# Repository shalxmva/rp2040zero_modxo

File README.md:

# rp2040zero_modxo
rp2040zero carrier board for modxo

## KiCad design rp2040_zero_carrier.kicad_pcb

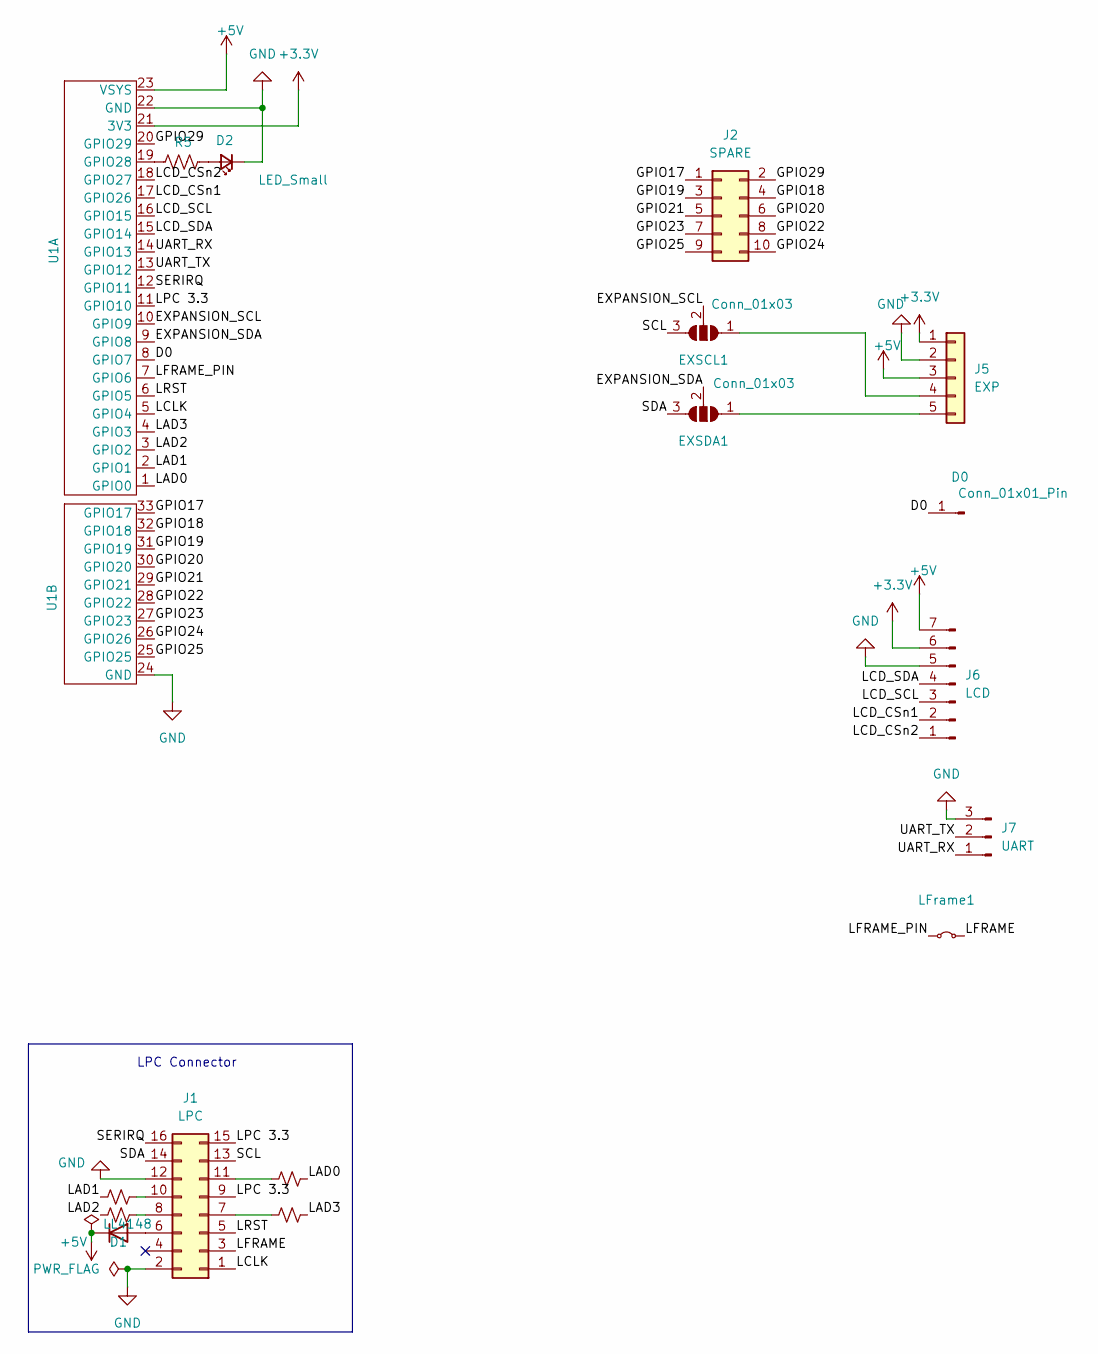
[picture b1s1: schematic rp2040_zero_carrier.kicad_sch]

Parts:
D0: Conn_01x01_Pin; SolderJumper-2_P1.3mm_Bridged2Bar_RoundedPad1.0x1.5mm
D1: LL4148; D_MiniMELF
D2: LED_Small; LED_0805_2012Metric_Pad1.15x1.40mm_HandSolder
EXSCL1: Conn_01x03; SolderJumper-3_P1.3mm_Bridged12_RoundedPad1.0x1.5mm
EXSDA1: Conn_01x03; SolderJumper-3_P1.3mm_Bridged12_RoundedPad1.0x1.5mm
J1: LPC; PinSocket_2x08_P2.54mm_Vertical
J2: SPARE; PinHeader_2x05_P2.54mm_Vertical
J5: EXP; PinHeader_1x05_P2.54mm_Vertical
J6: LCD; PinHeader_1x07_P2.54mm_Vertical
J7: UART; PinHeader_1x03_P2.54mm_Vertical
LFrame1: Jumper_2_Small_Bridged; SolderJumper-2_P1.3mm_Bridged_RoundedPad1.0x1.5mm
R1, R2, R3, R4: 100; R_0805_2012Metric_Pad1.20x1.40mm_HandSolder
R5: R_US; R_0805_2012Metric_Pad1.20x1.40mm_HandSolder
U1: RP2040 Zero

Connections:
+3.3V: J5.1, J6.6, U1.21 (3V3)
+5V: D1.1 (K), J5.3, J6.7, U1.23 (VSYS)
/D0: D0.1, U1.8 (GPIO7)
/EXPANSION_SCL: EXSCL1.2 (C), U1.10 (GPIO9)
/EXPANSION_SDA: EXSDA1.2 (C), U1.9 (GPIO8)
/GPIO17: J2.1, U1.33 (GPIO17)
/GPIO18: J2.4, U1.32 (GPIO18)
/GPIO19: J2.3, U1.31 (GPIO19)
/GPIO20: J2.6, U1.30 (GPIO20)
/GPIO21: J2.5, U1.29 (GPIO21)
/GPIO22: J2.8, U1.28 (GPIO22)
/GPIO23: J2.7, U1.27 (GPIO23)
/GPIO24: J2.10, U1.26 (GPIO26)
/GPIO25: J2.9, U1.25 (GPIO25)
/GPIO29: J2.2, U1.20 (GPIO29)
/LAD0: R1.2, U1.1 (GPIO0)
/LAD1: R2.1, U1.2 (GPIO1)
/LAD2: R3.1, U1.3 (GPIO2)
/LAD3: R4.2, U1.4 (GPIO3)
/LCD_CSn1: J6.2, U1.17 (GPIO26)
/LCD_CSn2: J6.1, U1.18 (GPIO27)
/LCD_SCL: J6.3, U1.16 (GPIO15)
/LCD_SDA: J6.4, U1.15 (GPIO14)
/LCLK: J1.1, U1.5 (GPIO4)
/LFRAME: J1.3, LFrame1.2 (B)
/LFRAME_PIN: LFrame1.1 (A), U1.7 (GPIO6)
/LPC 3.3: J1.9, J1.15, U1.11 (GPIO10)
/LRST: J1.5, U1.6 (GPIO5)
/SCL: EXSCL1.3 (B), J1.13
/SDA: EXSDA1.3 (B), J1.14
/SERIRQ: J1.16, U1.12 (GPIO11)
/UART_RX: J7.1, U1.14 (GPIO13)
/UART_TX: J7.2, U1.13 (GPIO12)
GND: D2.1 (K), J1.2, J1.12, J5.2, J6.5, J7.3, U1.22 (GND), U1.24 (GND)
unnamed: D1.2 (A), J1.6
unnamed: D2.2 (A), R5.2
unnamed: EXSCL1.1 (A), J5.4
unnamed: EXSDA1.1 (A), J5.5
unnamed: J1.7, R4.1
unnamed: J1.8, R3.2
unnamed: J1.10, R2.2
unnamed: J1.11, R1.1
unnamed: R5.1, U1.19 (GPIO28)

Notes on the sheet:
LPC Connector

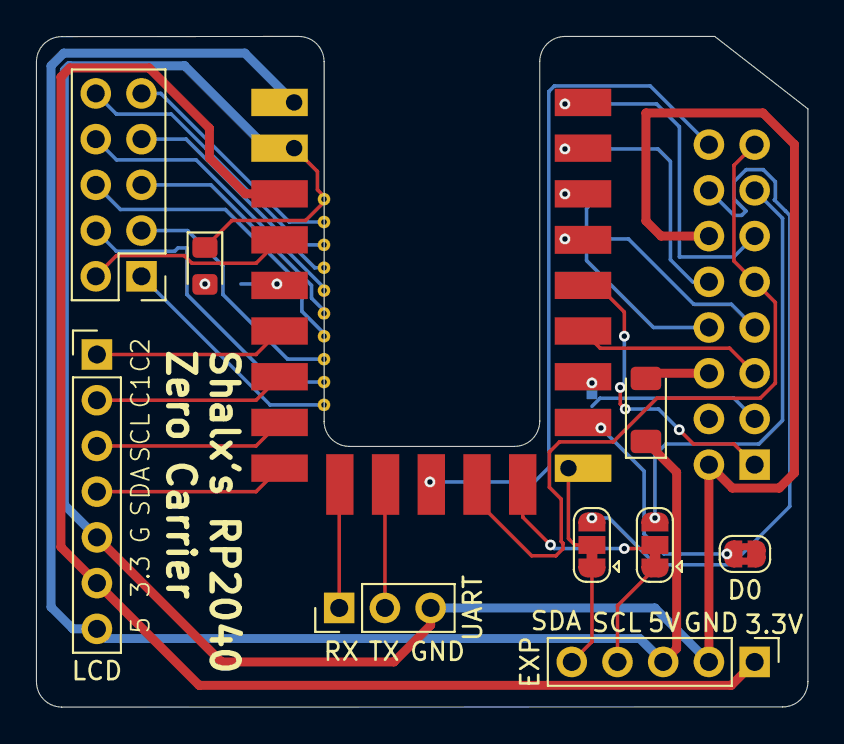
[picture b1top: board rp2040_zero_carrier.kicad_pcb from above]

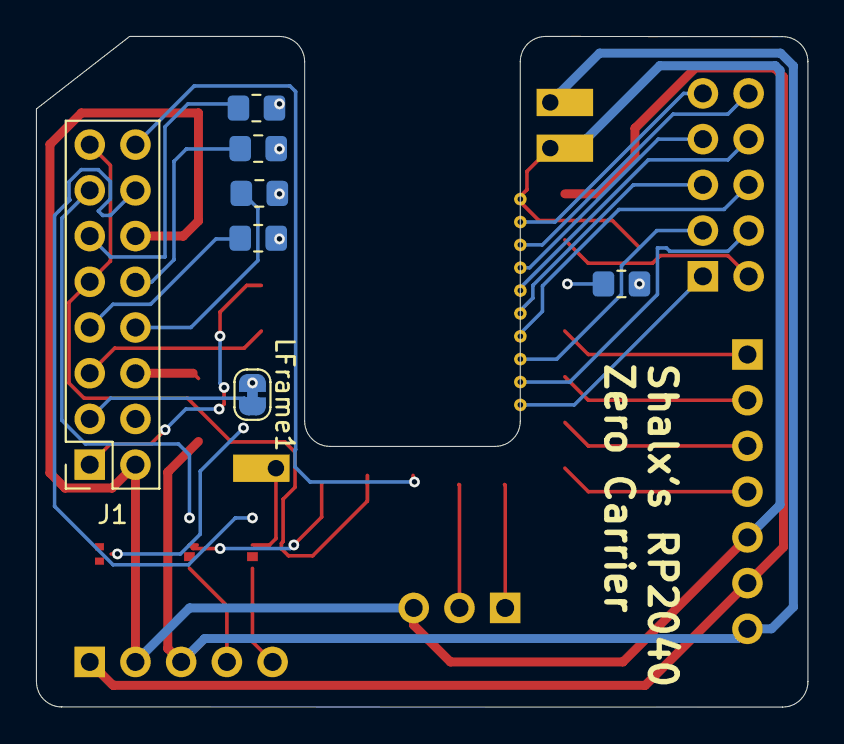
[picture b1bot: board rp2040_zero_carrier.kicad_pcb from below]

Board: 2 copper layers, 42.9 x 37.3 mm, 17 parts (7 on the bottom side), 43 nets.

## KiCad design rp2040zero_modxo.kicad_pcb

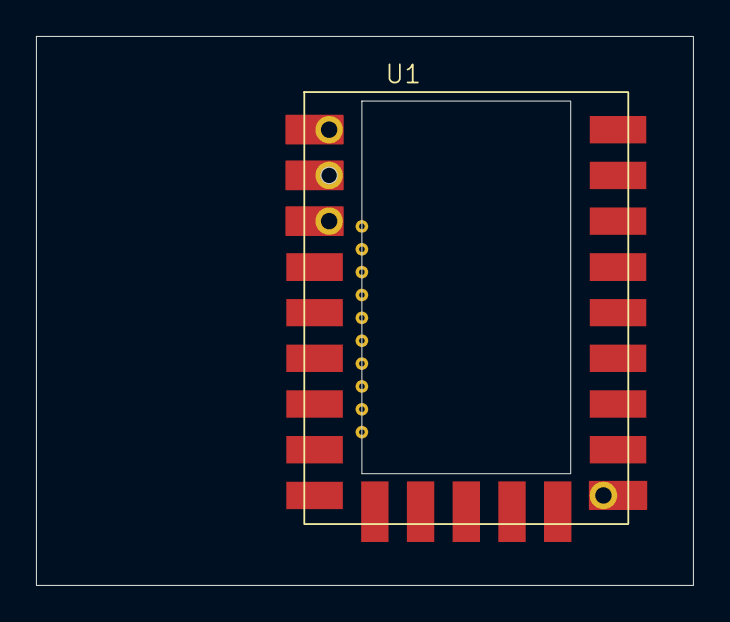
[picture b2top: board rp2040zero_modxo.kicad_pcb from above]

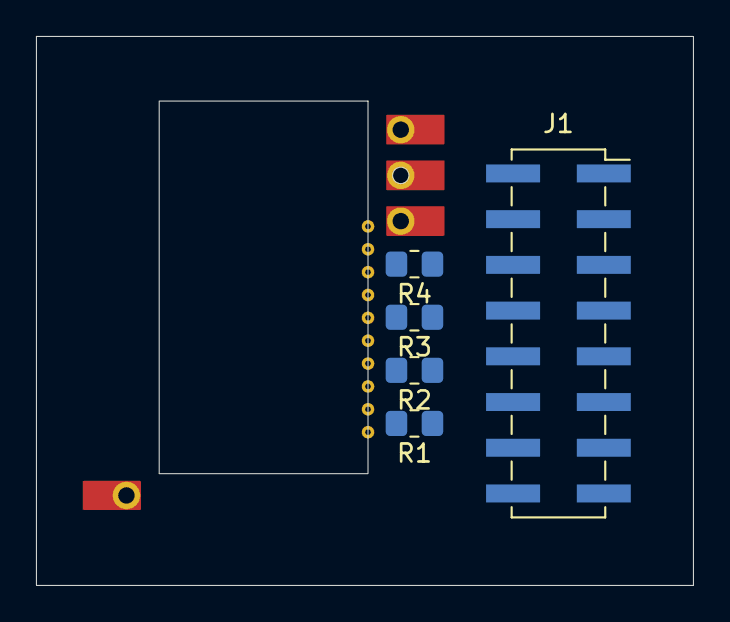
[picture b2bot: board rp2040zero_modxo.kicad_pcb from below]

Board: 2 copper layers, 36.5 x 30.5 mm, 6 parts (5 on the bottom side), 10 nets, no tracks yet.

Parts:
J1: Conn_02x08_Odd_Even; PinSocket_2x08_P2.54mm_Vertical_SMD
R1, R2, R3, R4: 100; R_0805_2012Metric_Pad1.20x1.40mm_HandSolder
U1: RP2040 Zero

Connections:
+5V: J1.6, U1.23 (VSYS)
/LAD0: R1.2, U1.28 (GPIO22)
/LAD1: R2.1, U1.27 (GPIO23)
/LAD2: R3.1, U1.26 (GPIO26)
/LAD3: R4.2, U1.25 (GPIO25)
/LCLK: J1.1, U1.29 (GPIO21)
/LFRAME: J1.3, U1.31 (GPIO19)
/LPC 3.3: J1.9, J1.15, U1.33 (GPIO17)
/LRST: J1.5, U1.30 (GPIO20)
GND: J1.2, J1.12, U1.22 (GND), U1.24 (GND)

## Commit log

2024-09-08 Initial files
2024-09-08 Added gitmodule rp2040zero footprint
2024-12-13 Board routed with latest footprint
2025-01-22 Updated rp2040 zero footprint
